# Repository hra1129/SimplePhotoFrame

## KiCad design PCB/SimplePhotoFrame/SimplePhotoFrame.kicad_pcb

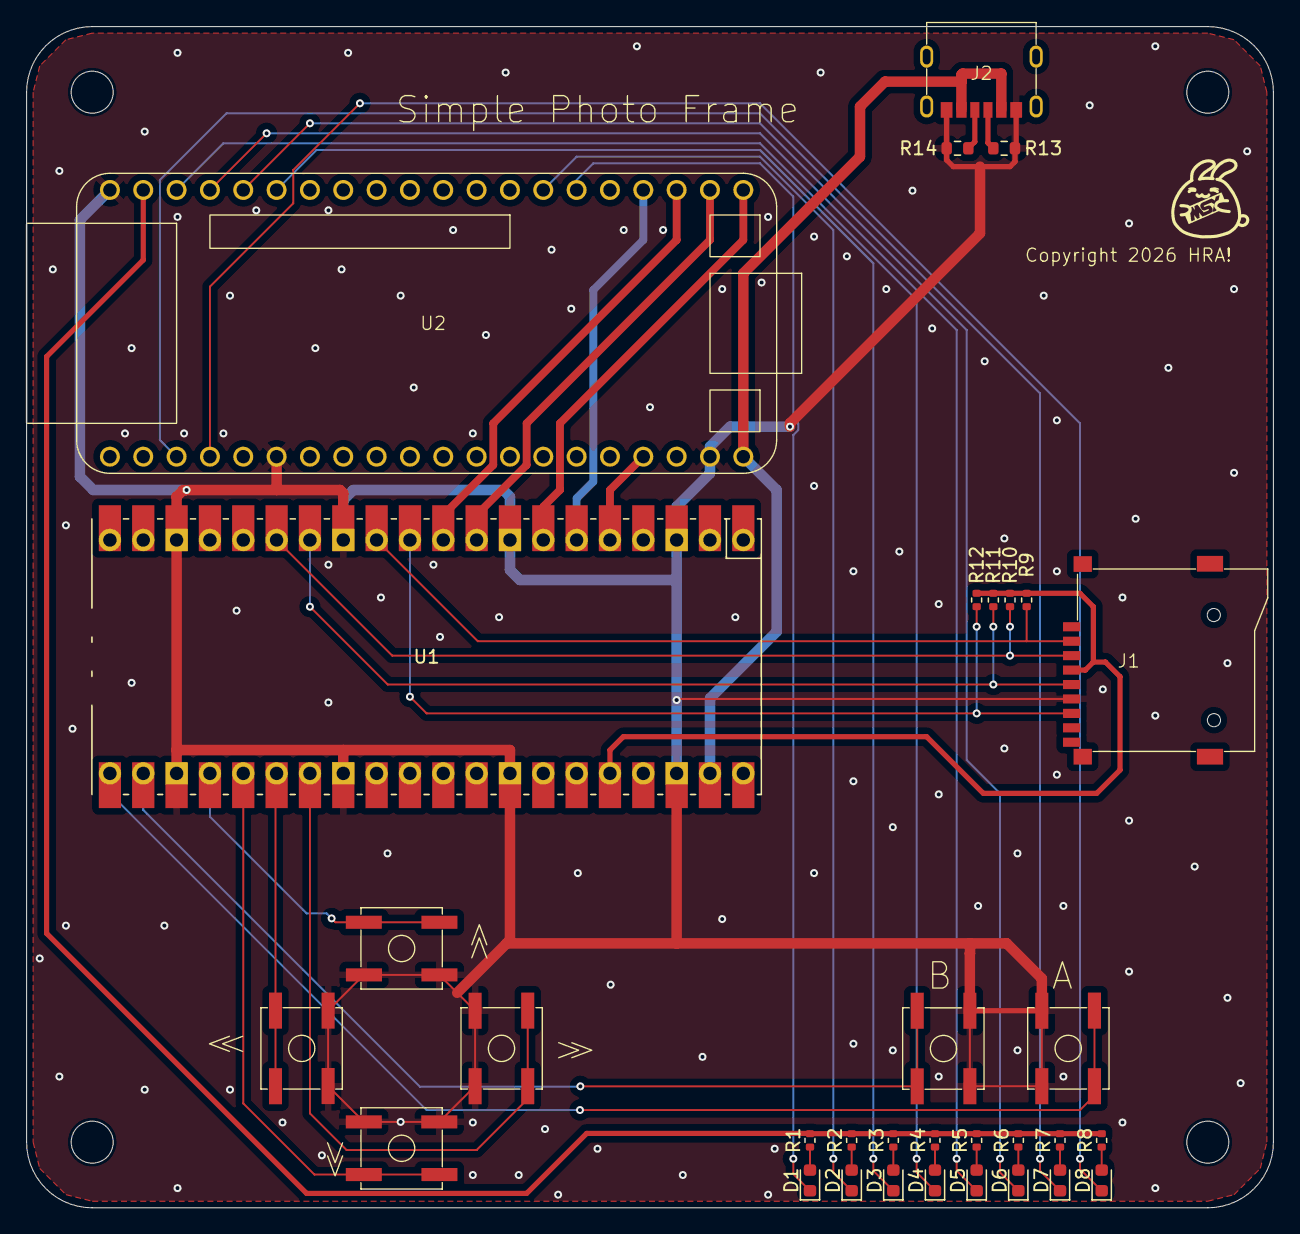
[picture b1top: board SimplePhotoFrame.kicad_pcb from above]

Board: 2 copper layers, 95.0 x 90.0 mm, 33 parts (0 on the bottom side), 37 nets.

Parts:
D1, D2, D3, D4, D5, D6, D7, D8: LED; LED_0603_1608Metric
G1: LOGO; usa_10x7
J1: Micro_SD_Card; MicroSD(C91145)
J2: USB_C_Receptacle_PowerOnly_6P; USB-C(C2927029)
R1, R2, R3, R4, R5, R6, R7, R8: 330R; R_0402_1005Metric
R9, R10, R11, R12: 22K; R_0402_1005Metric
R13, R14: 5.1K; R_0603_1608Metric
SW1, SW2, SW3, SW4, SW5, SW6: SW_MEC_5G; TactileSwitch(C19724057)
U1: RPi_Pico_SMD_TH
U2: TangNano20K

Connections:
3V3: R1.2, R2.2, R3.2, R4.2, R5.2, R6.2, R7.2, R8.2, U2.19 (3V3)
+5V: J2.A9 (VBUS), U1.39 (VSYS(+5V)), U2.40 (5V)
FPGA_SPI_CS_N: U1.7 (FPGA_SPI_CS_N(GP5)), U2.1 (FPGA_SPI_CS_N(73))
FPGA_SPI_INTR: U1.5 (FPGA_SPI_INTR(GP3)), U2.37 (FPGA_SPI_INTR(80))
FPGA_SPI_MISO: U1.6 (FPGA_SPI_MISO(GP4)), U2.4 (FPGA_SPI_MISO(85))
FPGA_SPI_MOSI: U1.10 (FPGA_SPI_MOSI(GP7)), U2.3 (FPGA_SPI_MOSI(75))
FPGA_SPI_SCK: U1.9 (FPGA_SPI_SCK(GP6)), U2.2 (FPGA_SPI_SCK(74))
GND: J1.6 (VSS), J2.A12 (GND), R13.2, R14.2, SW1.3 (B), SW2.3 (B), SW3.3 (B), SW4.3 (B), SW5.3 (B), SW6.3 (B), U1.3 (GND), U1.8 (GND), U1.13 (GND), U1.18 (GND), U1.23 (GND), U1.28 (GND), U1.33 (GND), U1.38 (GND), U2.20 (GND), U2.26 (GND), U2.39 (GND)
LED0: D1.1 (K), U2.6 (LED0(15))
LED1: D2.1 (K), U2.7 (LED1(16))
LED2: D3.1 (K), U2.15 (LED2(17))
LED3: D4.1 (K), U2.18 (LED3(18))
LED4: D5.1 (K), U2.17 (LED4(19))
LED5: D6.1 (K), U2.16 (LED5(20))
LED6: D7.1 (K), U2.23 (LED6(71))
LED7: D8.1 (K), U2.24 (LED7(72))
unnamed: D1.2 (A), R1.1
unnamed: D2.2 (A), R2.1
unnamed: D3.2 (A), R3.1
unnamed: D4.2 (A), R4.1
unnamed: D5.2 (A), R5.1
unnamed: D6.2 (A), R6.1
unnamed: D7.2 (A), R7.1
unnamed: D8.2 (A), R8.1
unnamed: J2.A5 (CC1), R13.1
unnamed: J2.B5 (CC2), R14.1
SD_SPI_CS_N: J1.2 (DAT3/CD), R9.1, U1.12 (SD_SPI_CS_N(GP9))
SD_SPI_MISO: J1.7 (DAT0), R12.1, U1.11 (SD_SPI_MISO(GP8))
SD_SPI_MOSI: J1.3 (CMD), R10.1, U1.15 (SD_SPI_MOSI(GP11))
SD_SPI_SCK: J1.5 (CLK), R11.1, U1.14 (SD_SPI_SCK(GP10))
SD_VDD: J1.4 (VDD), R9.2, R10.2, R11.2, R12.2, U1.36 (3V3)
SW_A: SW1.1 (A), U1.21 (SW_A(GP16))
SW_B: SW2.1 (A), U1.22 (SW_B(GP17))
SW_D: SW4.1 (A), U1.25 (SW_D(GP19))
SW_L: SW5.1 (A), U1.26 (SW_L(GP20))
SW_R: SW6.1 (A), U1.27 (SW_R(GP21))
SW_U: SW3.1 (A), U1.24 (SW_U(GP18))

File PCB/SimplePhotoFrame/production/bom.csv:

Designator,Footprint,Quantity,Value,LCSC Part #
"D1, D2, D3, D4, D5, D6, D7, D8",0603,8,LED,C2286
J1,MicroSD(C91145),1,Micro_SD_Card,C91145
J2,USB-C(C2927029),1,USB_C_Receptacle_PowerOnly_6P,C2927029
"R1, R2, R3, R4, R5, R6, R7, R8",0402,8,330R,C12246
"R10, R11, R12, R9",0402,4,22K,C25768
"R13, R14",0603,2,5.1K,C23186
"SW1, SW2, SW3, SW4, SW5, SW6",TactileSwitch(C19724057),6,SW_MEC_5G,C19724057

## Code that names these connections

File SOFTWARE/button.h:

// -----------------------------------------------------------------------------
//	button.h
//	Copyright (C)2026 Takayuki Hara (HRA!)
//	
//	 Permission is hereby granted, free of charge, to any person obtaining a 
//	copy of this software and associated documentation files (the "Software"), 
//	to deal in the Software without restriction, including without limitation 
//	the rights to use, copy, modify, merge, publish, distribute, sublicense, 
//	and/or sell copies of the Software, and to permit persons to whom the 
//	Software is furnished to do so, subject to the following conditions:
//	
//	The above copyright notice and this permission notice shall be included in 
//	all copies or substantial portions of the Software.
//	
//	The Software is provided "as is", without warranty of any kind, express or 
//	implied, including but not limited to the warranties of merchantability, 
//	fitness for a particular purpose and noninfringement. In no event shall the 
//	authors or copyright holders be liable for any claim, damages or other 
//	liability, whether in an action of contract, tort or otherwise, arising 
//	from, out of or in connection with the Software or the use or other dealings 
//	in the Software.
// -----------------------------------------------------------------------------

#ifndef __BUTTON_H__
#define __BUTTON_H__

#include <stdint.h>

#define SW_A					(1u << 0)
#define SW_B					(1u << 1)
#define SW_U					(1u << 2)
#define SW_D					(1u << 3)
#define SW_L					(1u << 4)
#define SW_R					(1u << 5)

#define SW_ON					(1u)
#define SW_OFF					(0u)

void button_init( void );
uint8_t button_get( void );

#endif

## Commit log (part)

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2026-05-24 PCB Updated
2026-05-26 Add .editorconfig, .gitattributes, and .gitignore files for project configuration
2026-05-26 SDRAM Controller を追加
2026-05-31 SDRAMコントローラーのファイル名変更
2026-05-31 PLL追加
2026-05-31 PLL追加に対応
2026-05-31 DisplayController の一部を実装
2026-06-04 Pico2W firmware
2026-06-10 液晶パネルに表示が出た

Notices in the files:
PCB/SimplePhotoFrame/SimplePhotoFrame.kicad_pcb:
Copyright 2026 HRA!
